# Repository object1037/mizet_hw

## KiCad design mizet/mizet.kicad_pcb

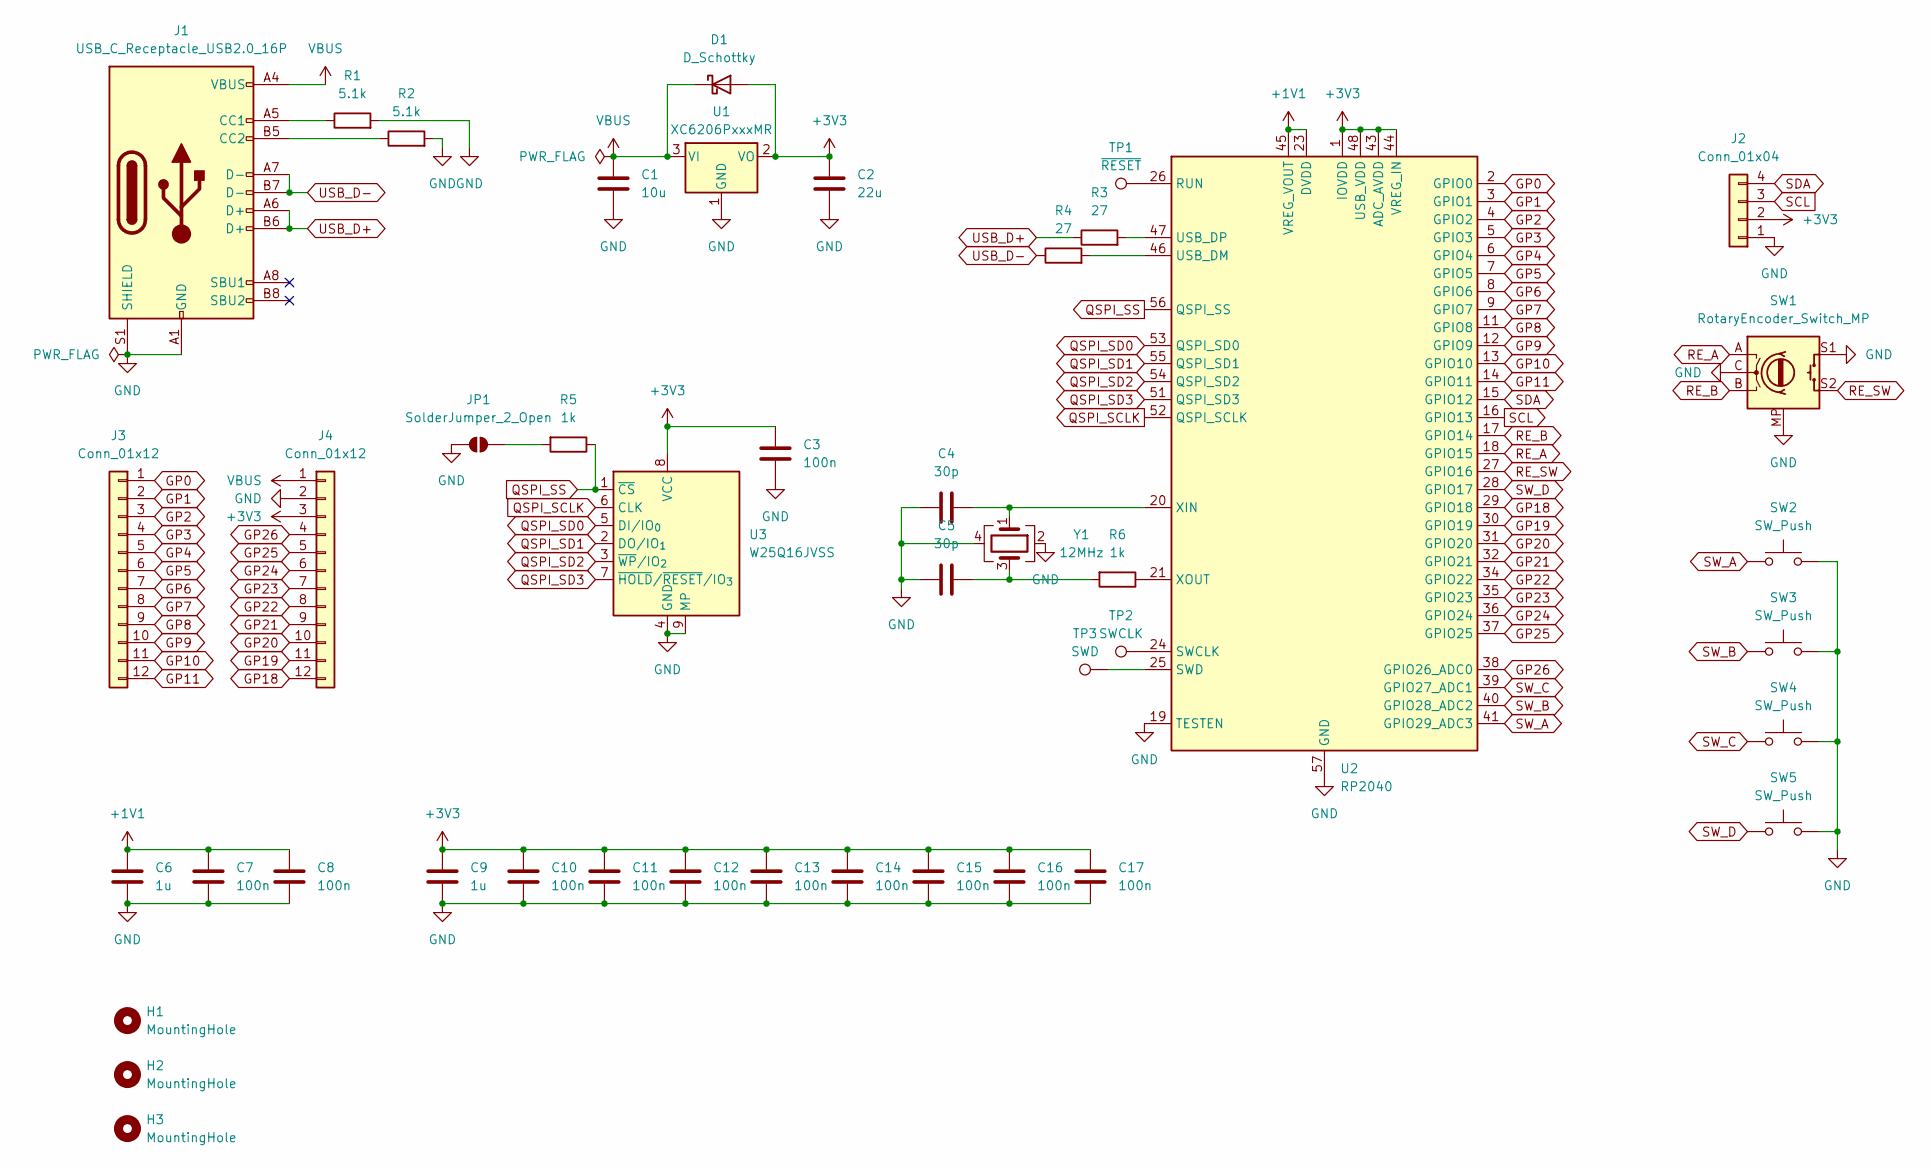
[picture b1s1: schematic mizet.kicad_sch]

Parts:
C1: 10u; C_0603_1608Metric_Pad1.08x0.95mm_HandSolder
C2: 22u; C_0603_1608Metric_Pad1.08x0.95mm_HandSolder
C3, C7, C8, C10, C11, C12, C13, C14, C15, C16, C17: 100n; C_0402_1005Metric_Pad0.74x0.62mm_HandSolder
C4, C5: 30p; C_0402_1005Metric_Pad0.74x0.62mm_HandSolder
C6, C9: 1u; C_0402_1005Metric_Pad0.74x0.62mm_HandSolder
D1: D_Schottky; D_SOD-123
H1, H2, H3: MountingHole; MountingHole_2.2mm_M2
J1: USB_C_Receptacle_USB2.0_16P; USB_C_Receptacle_HRO_TYPE-C-31-M-12
J2: Conn_01x04; PinSocket_1x04_P2.54mm_Vertical
J3, J4: Conn_01x12; PinHeader_1x12_P2.54mm_Vertical
JP1: SolderJumper_2_Open; SolderJumper-2_P1.3mm_Open_RoundedPad1.0x1.5mm
R1, R2: 5.1k; R_0402_1005Metric_Pad0.72x0.64mm_HandSolder
R3, R4: 27; R_0402_1005Metric_Pad0.72x0.64mm_HandSolder
R5, R6: 1k; R_0603_1608Metric_Pad0.98x0.95mm_HandSolder
SW1: RotaryEncoder_Switch_MP; RotaryEncoder_Alps_EC12E-Switch_Vertical_H20mm
SW2, SW3, SW4, SW5: SW_Push; tact_sw_smd
TP1: ~{RESET}; TestPoint_Pad_D1.5mm
TP2: SWCLK; PinHeader_1x01_P2.54mm_Horizontal
TP3: SWD; PinHeader_1x01_P2.54mm_Horizontal
U1: XC6206PxxxMR; SOT-23-3
U2: RP2040; RP2040-QFN-56
U3: W25Q16JVSS; Winbond_USON-8-1EP_3x2mm_P0.5mm_EP0.2x1.6mm
Y1: 12MHz; Crystal_SMD_3225-4Pin_3.2x2.5mm

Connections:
+1V1: C6.1, C7.1, C8.1, U2.23 (DVDD), U2.45 (VREG_VOUT), U2.50 (DVDD)
+3V3: C2.1, C3.1, C9.1, C10.1, C11.1, C12.1, C13.1, C14.1, C15.1, C16.1, C17.1, D1.2 (A), J2.2, J4.3, U1.2 (VO), U2.1 (IOVDD), U2.10 (IOVDD), U2.22 (IOVDD), U2.33 (IOVDD), U2.42 (IOVDD), U2.43 (ADC_AVDD), U2.44 (VREG_IN), U2.48 (USB_VDD), U2.49 (IOVDD), U3.8 (VCC)
GND: C1.2, C2.2, C3.2, C4.1, C5.1, C6.2, C7.2, C8.2, C9.2, C10.2, C11.2, C12.2, C13.2, C14.2, C15.2, C16.2, C17.2, J1.A1 (GND), J1.A12 (GND), J1.B1 (GND), J1.B12 (GND), J1.S1 (SHIELD), J2.1, J4.2, JP1.1 (A), R1.2, R2.2, SW1.C, SW1.MP, SW1.S1, SW2.1, SW3.1, SW4.1, SW5.1, U1.1 (GND), U2.19 (TESTEN), U2.57 (GND), U3.4 (GND), U3.9 (MP), Y1.2, Y1.4
GP0: J3.1, U2.2 (GPIO0)
GP1: J3.2, U2.3 (GPIO1)
GP2: J3.3, U2.4 (GPIO2)
GP3: J3.4, U2.5 (GPIO3)
GP4: J3.5, U2.6 (GPIO4)
GP5: J3.6, U2.7 (GPIO5)
GP6: J3.7, U2.8 (GPIO6)
GP7: J3.8, U2.9 (GPIO7)
GP8: J3.9, U2.11 (GPIO8)
GP9: J3.10, U2.12 (GPIO9)
GP10: J3.11, U2.13 (GPIO10)
GP11: J3.12, U2.14 (GPIO11)
GP18: J4.12, U2.29 (GPIO18)
GP19: J4.11, U2.30 (GPIO19)
GP20: J4.10, U2.31 (GPIO20)
GP21: J4.9, U2.32 (GPIO21)
GP22: J4.8, U2.34 (GPIO22)
GP23: J4.7, U2.35 (GPIO23)
GP24: J4.6, U2.36 (GPIO24)
GP25: J4.5, U2.37 (GPIO25)
GP26: J4.4, U2.38 (GPIO26_ADC0)
unnamed: C5.2, R6.2, Y1.3
unnamed: J1.A5 (CC1), R1.1
unnamed: J1.B5 (CC2), R2.1
unnamed: JP1.2 (B), R5.2
unnamed: TP1.1, U2.26 (RUN)
unnamed: TP2.1, U2.24 (SWCLK)
unnamed: TP3.1, U2.25 (SWD)
unnamed: R4.2, U2.46 (USB_DM)
unnamed: R3.2, U2.47 (USB_DP)
unnamed: C4.2, U2.20 (XIN), Y1.1
unnamed: R6.1, U2.21 (XOUT)
QSPI_SCLK: U2.52 (QSPI_SCLK), U3.6 (CLK)
QSPI_SD0: U2.53 (QSPI_SD0), U3.5 (DI/IO_{0})
QSPI_SD1: U2.55 (QSPI_SD1), U3.2 (DO/IO_{1})
QSPI_SD2: U2.54 (QSPI_SD2), U3.3 (~WP/IO_{2})
QSPI_SD3: U2.51 (QSPI_SD3), U3.7 (~HOLD/~RESET/IO_{3})
QSPI_SS: R5.1, U2.56 (QSPI_SS), U3.1 (~CS)
RE_A: SW1.A, U2.18 (GPIO15)
RE_B: SW1.B, U2.17 (GPIO14)
RE_SW: SW1.S2, U2.27 (GPIO16)
SCL: J2.3, U2.16 (GPIO13)
SDA: J2.4, U2.15 (GPIO12)
SW_A: SW2.2, U2.41 (GPIO29_ADC3)
SW_B: SW3.2, U2.40 (GPIO28_ADC2)
SW_C: SW4.2, U2.39 (GPIO27_ADC1)
SW_D: SW5.2, U2.28 (GPIO17)
USB_D+: J1.A6 (D+), J1.B6 (D+), R3.1
USB_D-: J1.A7 (D-), J1.B7 (D-), R4.1
VBUS: C1.1, D1.1 (K), J1.A4 (VBUS), J1.A9 (VBUS), J1.B4 (VBUS), J1.B9 (VBUS), J4.1, U1.3 (VI)

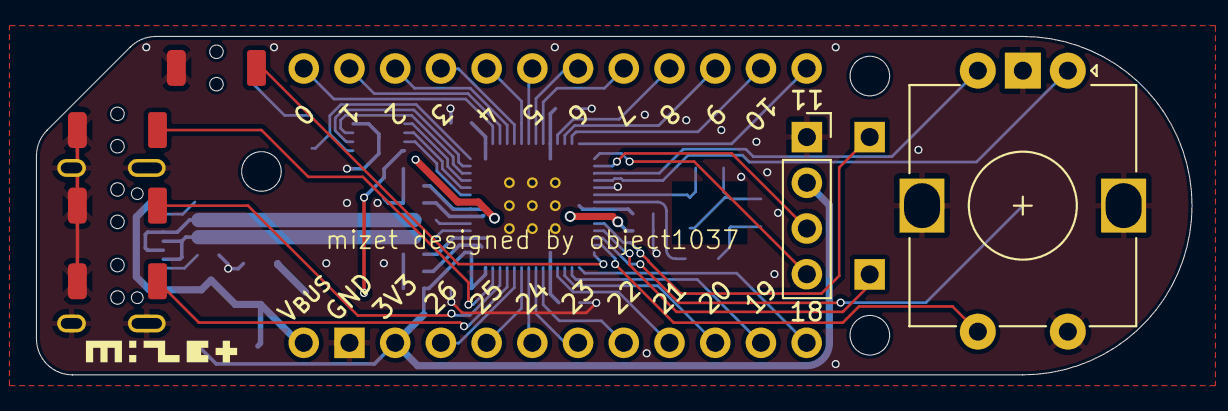
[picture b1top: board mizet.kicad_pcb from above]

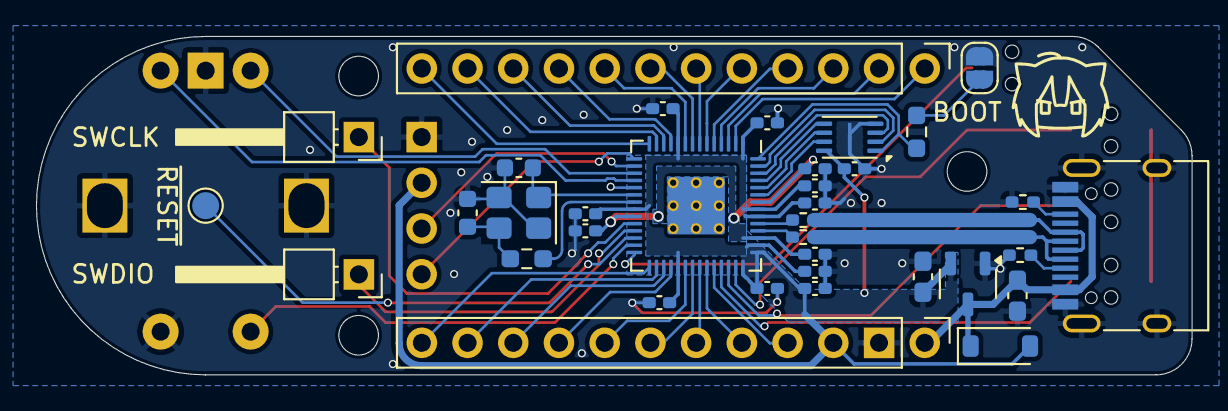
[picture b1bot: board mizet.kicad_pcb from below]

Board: 2 copper layers, 64.2 x 18.8 mm, 44 parts (35 on the bottom side), 53 nets.

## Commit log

2026-03-01 init
2026-03-01 schematic
2026-03-04 basic pcb
2026-03-05 update pcb
2026-03-07 add mounting holes
2026-03-07 generate jlcpcb files
